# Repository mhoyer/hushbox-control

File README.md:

# ESP32 - Fan Control

## Resources

### ESP32 Pin Out

- [ESP32 - General Pinout](https://randomnerdtutorials.com/esp32-pinout-reference-gpios/)
- [Doit ESP32 DevKit - Pinout](https://github.com/playelek/pinout-doit-32devkitv1)

### Fan Control

- [ESP32 Fan Controller](https://github.com/KlausMu/esp32-fan-controller)
- [4-Wire PWM Controlled Fans - Pinout](https://allpinouts.org/pinouts/connectors/motherboards/motherboard-cpu-4-pin-fan/)
- [How to read RPM from 3-wire fan](https://electronics.stackexchange.com/a/214082)
- [Raspberry Pi - Building a PWM Fan Controller with DotNet IoT](http://blog.timwheeler.io/building-a-pwm-fan-controller-with-dotnet-iot/)
- [IRLML2502 - MOSFET for switching the fan on/off](https://www.infineon.com/dgdl/irlml2502pbf.pdf)
- [0x1A Transistor (MOSFET) als Schalter](https://www.youtube.com/watch?v=d1yEUiCsBWc)

### Temperature Reading

- [Dallas DS18B20 - 1-Wire Digital Thermometer](https://datasheets.maximintegrated.com/en/ds/DS18B20.pdf)
- [Interfacing DS18B20 1-Wire Digital Temperature Sensor with Arduino](https://lastminuteengineers.com/ds18b20-arduino-tutorial/)

## Micropython

Flashing the firmware:

1. Press and hold the BOOT button and run: `esptool.py --chip esp32 --port /dev/ttyUSB0 erase_flash`
2. Now run: `esptool.py --chip esp32 --port /dev/ttyUSB0 --baud 460800 write_flash -z 0x1000 esp32-idf4-20200902-v1.13.bin`

I tested `esp32-idf4-20191220-v1.12.bin` and `esp32-idf4-20191220-v1.13.bin` from https://micropython.org/download/esp32/.

### Getting infos about ESP32

While the ESP32 is connected to the serial adaptor you can run this `esptool` command and instantly have to press the `BOOT` button on the ESP32:

```bash
$ ./esptool --baud 921600 flash_id
esptool.py v4.4
Found 1 serial ports
Serial port /dev/ttyUSB0
Connecting....
Detecting chip type... Unsupported detection protocol, switching and trying again...
Connecting....
Detecting chip type... ESP32
Chip is ESP32-D0WDQ6 (revision v1.0)
Features: WiFi, BT, Dual Core, Coding Scheme None
Crystal is 40MHz
MAC: 24:0a:c4:13:9a:90
Uploading stub...
Running stub...
Stub running...
Changing baud rate to 921600
Changed.
Manufacturer: c8
Device: 4016
Detected flash size: 4MB
Hard resetting via RTS pin...
```

#### Reading out the existing memory as a backup

```bash
./esptool --baud 921600 read_flash 0 0x400000 backup.bin
```

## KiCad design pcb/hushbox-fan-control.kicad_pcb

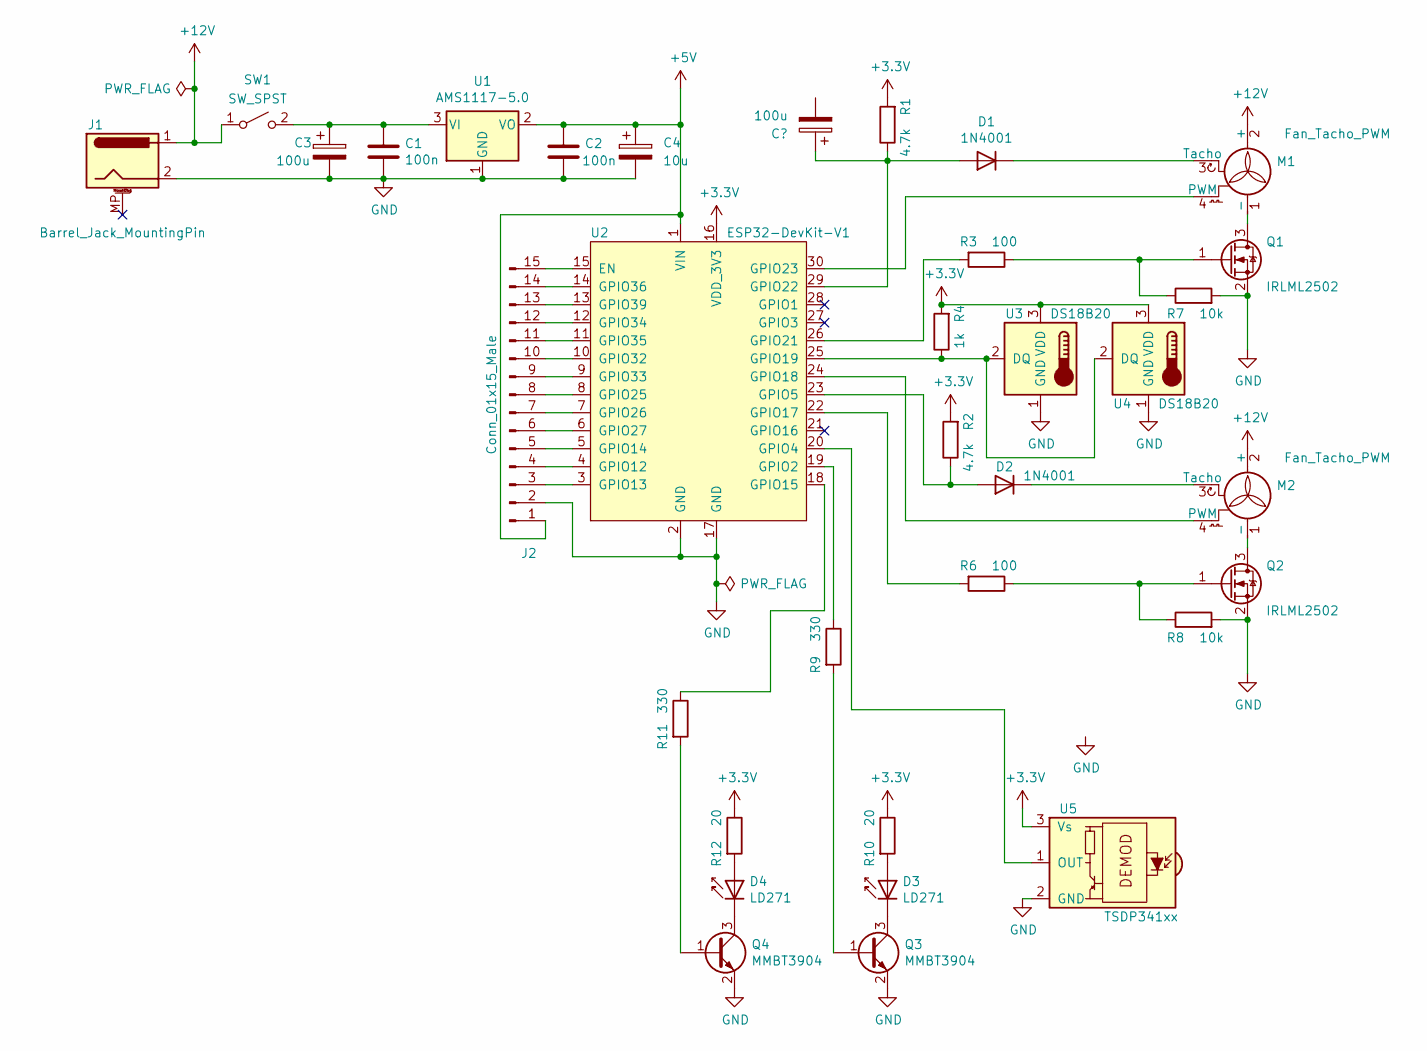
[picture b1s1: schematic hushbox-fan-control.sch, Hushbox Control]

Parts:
C1, C2: 100n; C_0805_2012Metric_Pad1.18x1.45mm_HandSolder
C3: 100u; CP_Radial_D8.0mm_P2.50mm
C4: 10u; CP_Radial_D5.0mm_P2.50mm
D1, D2: 1N4001; D_SMA_Handsoldering
D3, D4: LD271; JST_XH_S2B-XH-A_1x02_P2.50mm_Horizontal
J1: Barrel_Jack_MountingPin; BarrelJack_Horizontal
J2: Conn_01x15_Male; PinSocket_1x15_P2.54mm_Vertical
M1, M2: Fan_Tacho_PWM; FanPinHeader_1x04_P2.54mm_Vertical
Q1, Q2: IRLML2502; SOT-23_Handsoldering
Q3, Q4: MMBT3904; SOT-23_Handsoldering
R1, R2: 4.7k; R_0805_2012Metric_Pad1.20x1.40mm_HandSolder
R3, R6: 100; R_0805_2012Metric_Pad1.20x1.40mm_HandSolder
R4: 1k; R_0805_2012Metric_Pad1.20x1.40mm_HandSolder
R7, R8: 10k; R_0805_2012Metric_Pad1.20x1.40mm_HandSolder
R9, R11: 330; R_0805_2012Metric_Pad1.20x1.40mm_HandSolder
R10, R12: 20; R_0805_2012Metric_Pad1.20x1.40mm_HandSolder
SW1: SW_SPST; PinSocket_1x02_P2.54mm_Vertical
U1: AMS1117-5.0; SOT-223-3_TabPin2
U2: ESP32-DevKit-V1; Doit_ESP32_DevKit_V1
U3, U4: DS18B20; JST_XH_B3B-XH-A_1x03_P2.50mm_Vertical
U5: TSDP341xx; JST_XH_S3B-XH-A_1x03_P2.50mm_Horizontal

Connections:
+3V3: R1.2, R2.2, R4.2, R10.1, R12.1, U2.16 (VDD_3V3), U3.3 (VDD), U4.3 (VDD), U5.3 (Vs); also elsewhere on the board
+5V: C2.1, C4.1, J2.1, U1.2 (VO), U2.1 (VIN)
+12V: J1.1, M1.2 (+), M2.2 (+), SW1.1 (A)
GND: C1.2, C2.2, C3.2, C4.2, J1.2, J2.2, Q1.2 (S), Q2.2 (S), Q3.2 (E), Q4.2 (E), R7.2, R8.2, U1.1 (GND), U2.2 (GND), U2.17 (GND), U3.1 (GND), U4.1 (GND), U5.2 (GND)
unnamed: C1.1, C3.1, SW1.2 (B), U1.3 (VI)
unnamed: D1.1 (K), M1.3 (Tacho)
unnamed: D1.2 (A), R1.1, U2.29 (GPIO22)
unnamed: D2.1 (K), M2.3 (Tacho)
unnamed: D2.2 (A), R2.1, U2.23 (GPIO5)
unnamed: D3.1 (K), Q3.3 (C)
unnamed: D3.2 (A), R10.2
unnamed: D4.1 (K), Q4.3 (C)
unnamed: D4.2 (A), R12.2
unnamed: J2.3, U2.3 (GPIO13)
unnamed: J2.4, U2.4 (GPIO12)
unnamed: J2.5, U2.5 (GPIO14)
unnamed: J2.6, U2.6 (GPIO27)
unnamed: J2.7, U2.7 (GPIO26)
unnamed: J2.8, U2.8 (GPIO25)
unnamed: J2.9, U2.9 (GPIO33)
unnamed: J2.10, U2.10 (GPIO32)
unnamed: J2.11, U2.11 (GPIO35)
unnamed: J2.12, U2.12 (GPIO34)
unnamed: J2.13, U2.13 (GPIO39)
unnamed: J2.14, U2.14 (GPIO36)
unnamed: J2.15, U2.15 (EN)
unnamed: M1.1 (-), Q1.3 (D)
unnamed: M1.4 (PWM), U2.30 (GPIO23)
unnamed: M2.1 (-), Q2.3 (D)
unnamed: M2.4 (PWM), U2.24 (GPIO18)
unnamed: Q1.1 (G), R3.1, R7.1
unnamed: Q2.1 (G), R6.1, R8.1
unnamed: Q3.1 (B), R9.2
unnamed: Q4.1 (B), R11.2
unnamed: R3.2, U2.26 (GPIO21)
unnamed: R4.1, U2.25 (GPIO19), U3.2 (DQ), U4.2 (DQ)
unnamed: R6.2, U2.22 (GPIO17)
unnamed: R9.1, U2.19 (GPIO2)
unnamed: R11.1, U2.18 (GPIO15)
unnamed: U2.20 (GPIO4), U5.1 (OUT)

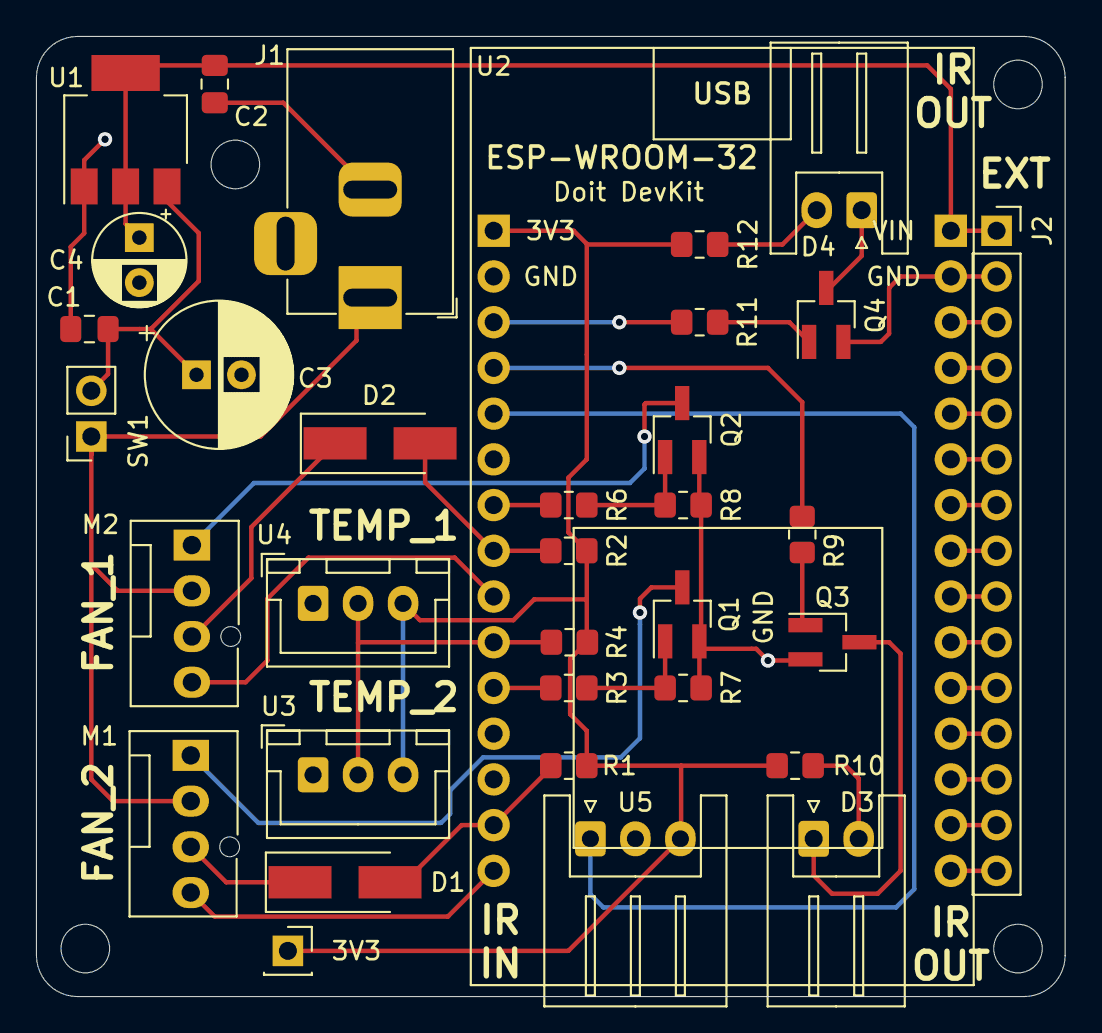
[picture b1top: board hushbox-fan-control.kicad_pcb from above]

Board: 2 copper layers, 57.1 x 53.3 mm, 34 parts (0 on the bottom side), 40 nets.

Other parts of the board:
3V3: PinSocket_1x01_P2.54mm_Vertical

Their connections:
+3V3: 3V3.1; also elsewhere on the board

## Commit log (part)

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2020-07-10 === initial commit
2020-07-10 `micropy init`
2020-07-20 extract LinearFanControl, RpmReader and TempReader
2020-07-20 add wifi support
2020-11-15 add hushbox PCB with schema and Doit ESP32 DevKit library
2020-11-15 add support for fan on/off switch
2020-11-15 add `send_metrics` helper
2020-11-15 fix temp_reader
2020-11-15 improve `wifi` helper to use `config.py`
2020-12-16 move python code into prototype subfolder
2020-12-16 improve pcb to v1.1 with IR support
2020-12-16 add initial `./native` PIO project
2020-12-16 add initial InfraredCtrl lib
2020-12-16 fix .gitignore to split up into subfolder
2020-12-16 add auto generated lib/README of native PIO project
2020-12-16 add initial MqttCtrl with WiFi connect logic
2021-01-01 add control-case 3d model
2021-01-01 add .gitignore
2021-01-02 fix nut holes dimensions and some refactorings
2021-01-02 add bottom preview helper
2021-01-02 add switch hole
2021-01-02 create MqttCtrl and WiFiCnx classes
2021-01-03 extend case width and add floor and wallmount holes
2021-01-03 add actual IR sending for movie_mode topic
2021-01-03 fix bug in MqttCtrl with subscription map
2021-01-09 fix tiny holes in dome
2021-01-09 adjust hole radius to let screws slide in smooth as butter
2021-01-09 add holes into top cover
2021-01-12 enable OTA
2021-01-12 move extracted classes from ./lib to ./src
2021-01-13 add TempReader
2021-01-13 improve TempReader to pass in pin on `setup`
2021-01-13 improve build size
2021-01-13 rename ota to OTA to be consistent
2021-01-15 add fan switch and binding to MQTT
2021-01-16 cleanup MqttCtrl.h
2021-01-16 add RPMReader
2021-01-16 refactor TempReader
2021-01-16 refactor InfraredCtrl
2021-01-16 reindent main.cpp
2021-01-16 add stdout monitoring interval
2021-01-16 fix RPM and TempReader to have dedicated local `_recent_values` variable
2021-01-16 add analogWrite lib and LinearFanSpeed functions
2021-01-17 refactor ota and linear-fan-speed
2021-01-17 refactor temperatures-reader
2021-01-17 refactor InfraredCtrl -> ir-io
2021-01-17 refactor config.h
2021-01-17 refactor rpm-reader
2022-12-28 update final selection of used gpio pins
2022-12-28 fix missing IR repeat for turnReceiverOff command
2022-12-28 add /fan_speed and /restart MQTT endpoints and finalize main loop
2022-12-28 finalize PCB layout
2022-12-28 add some more docs to README about backup of ESP32 memory
2022-12-28 add support for sending IR codes via MQTT directly
2025-01-18 fix build issues after update to latest framework and lib versions (also pinned current working versions)
